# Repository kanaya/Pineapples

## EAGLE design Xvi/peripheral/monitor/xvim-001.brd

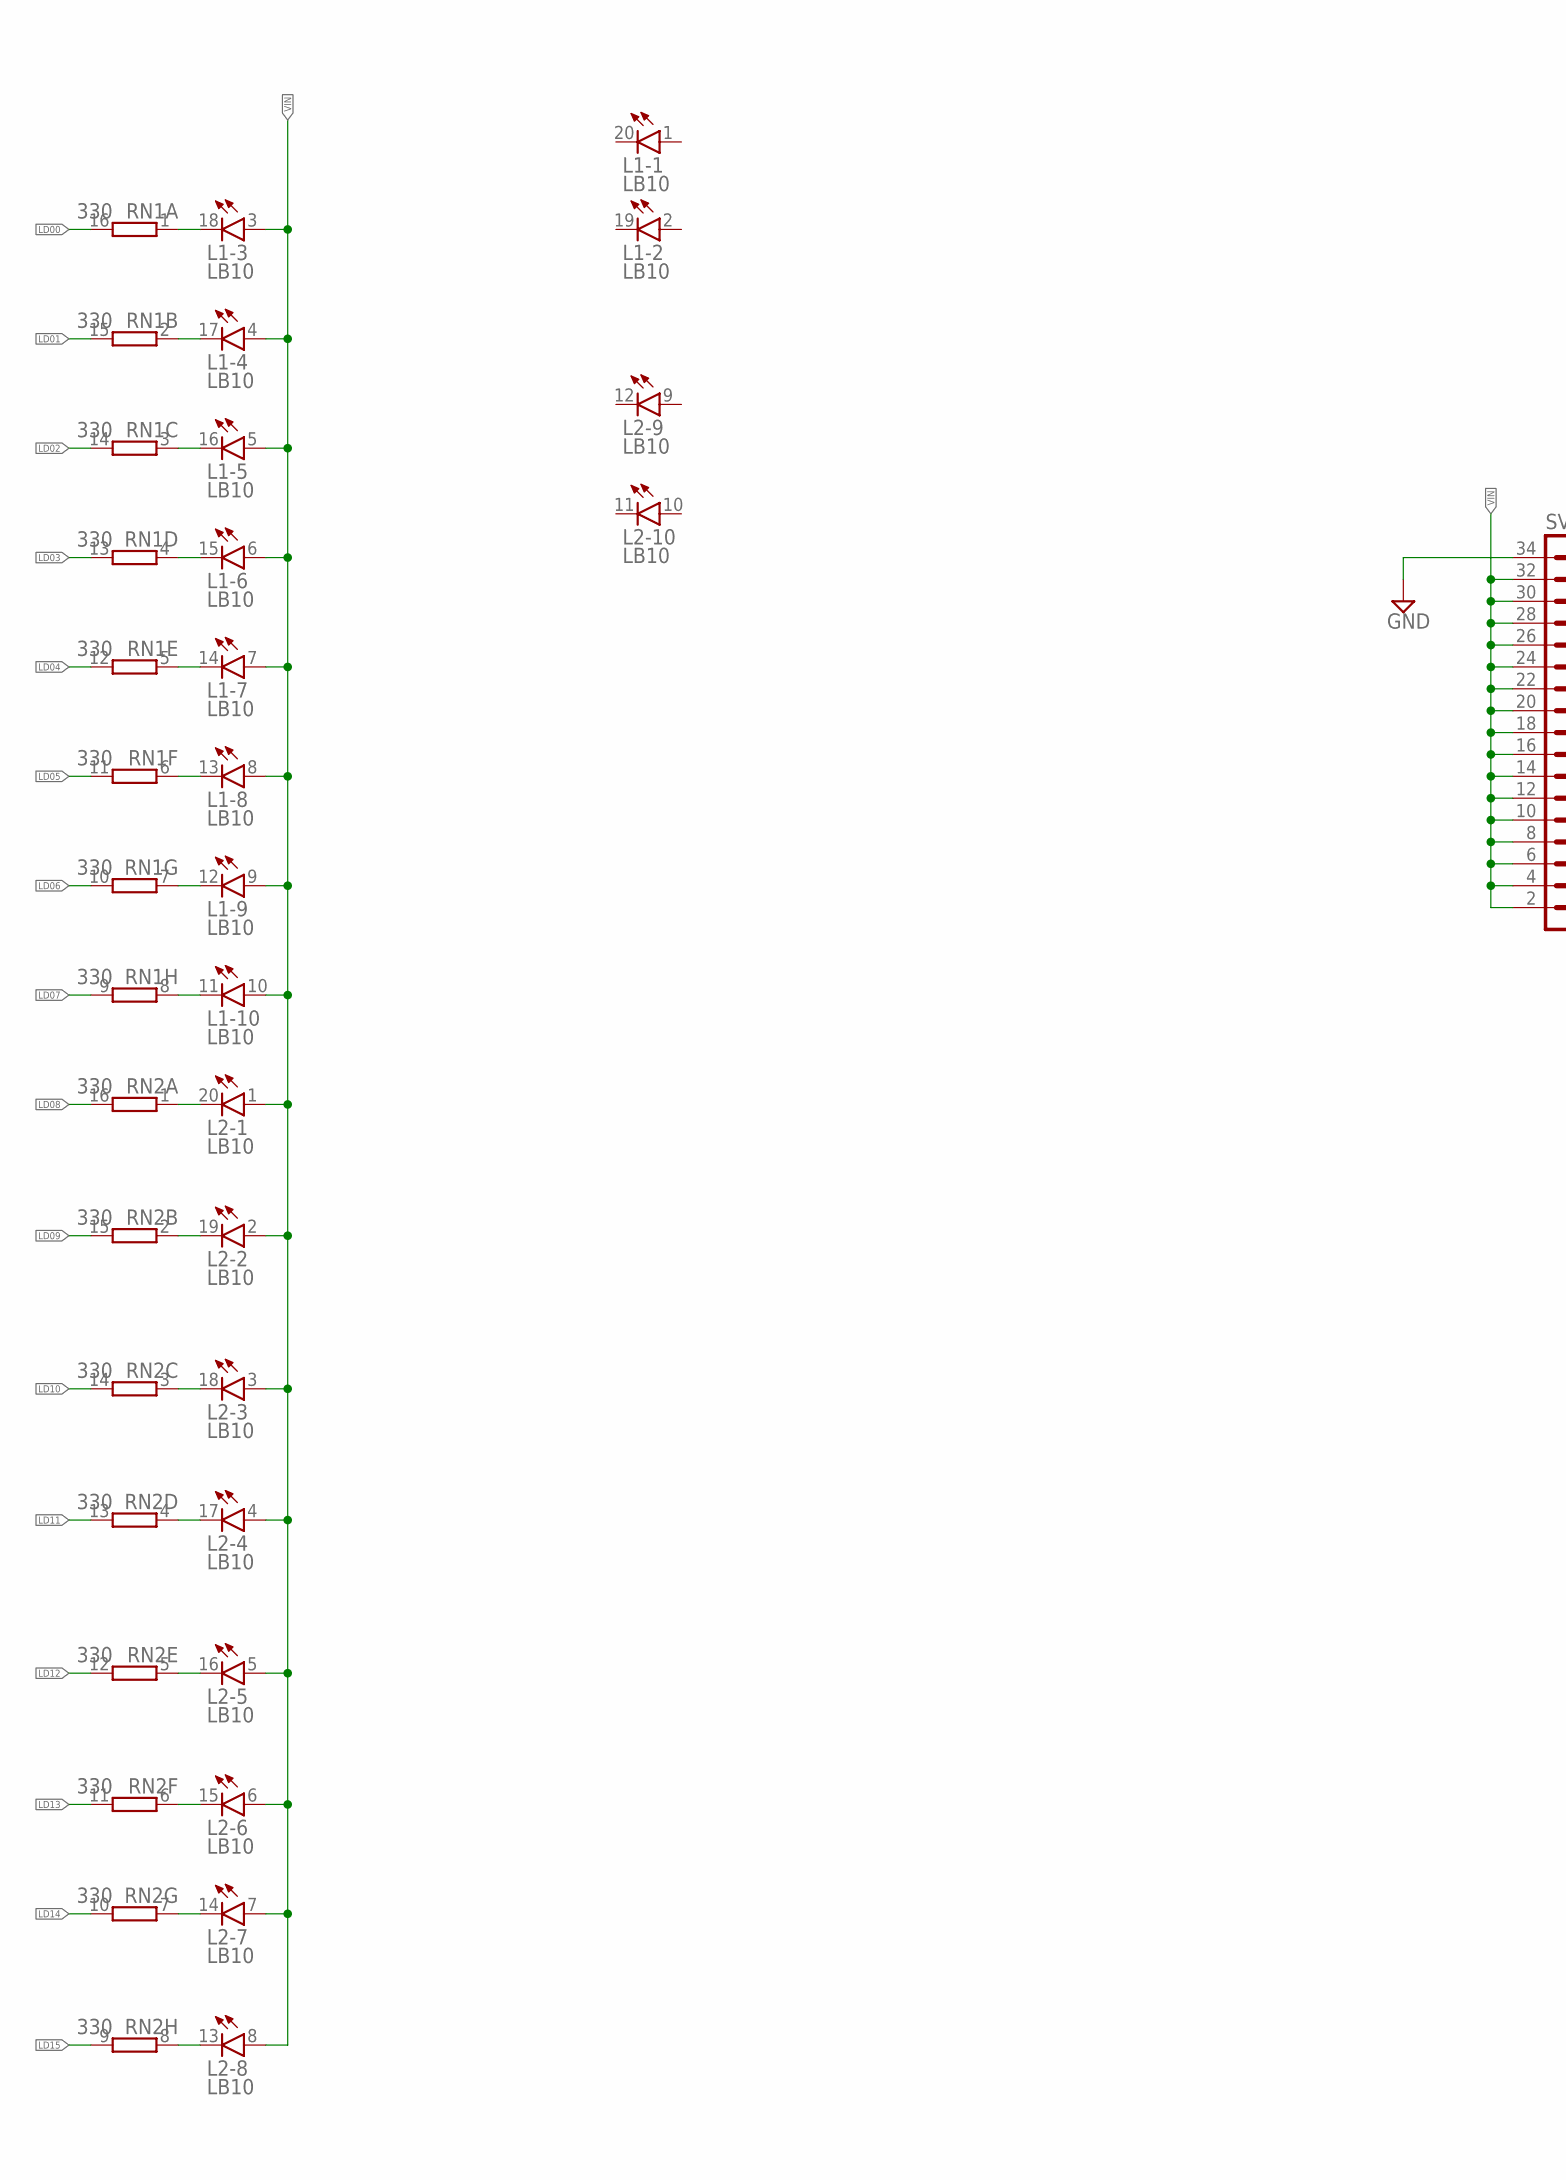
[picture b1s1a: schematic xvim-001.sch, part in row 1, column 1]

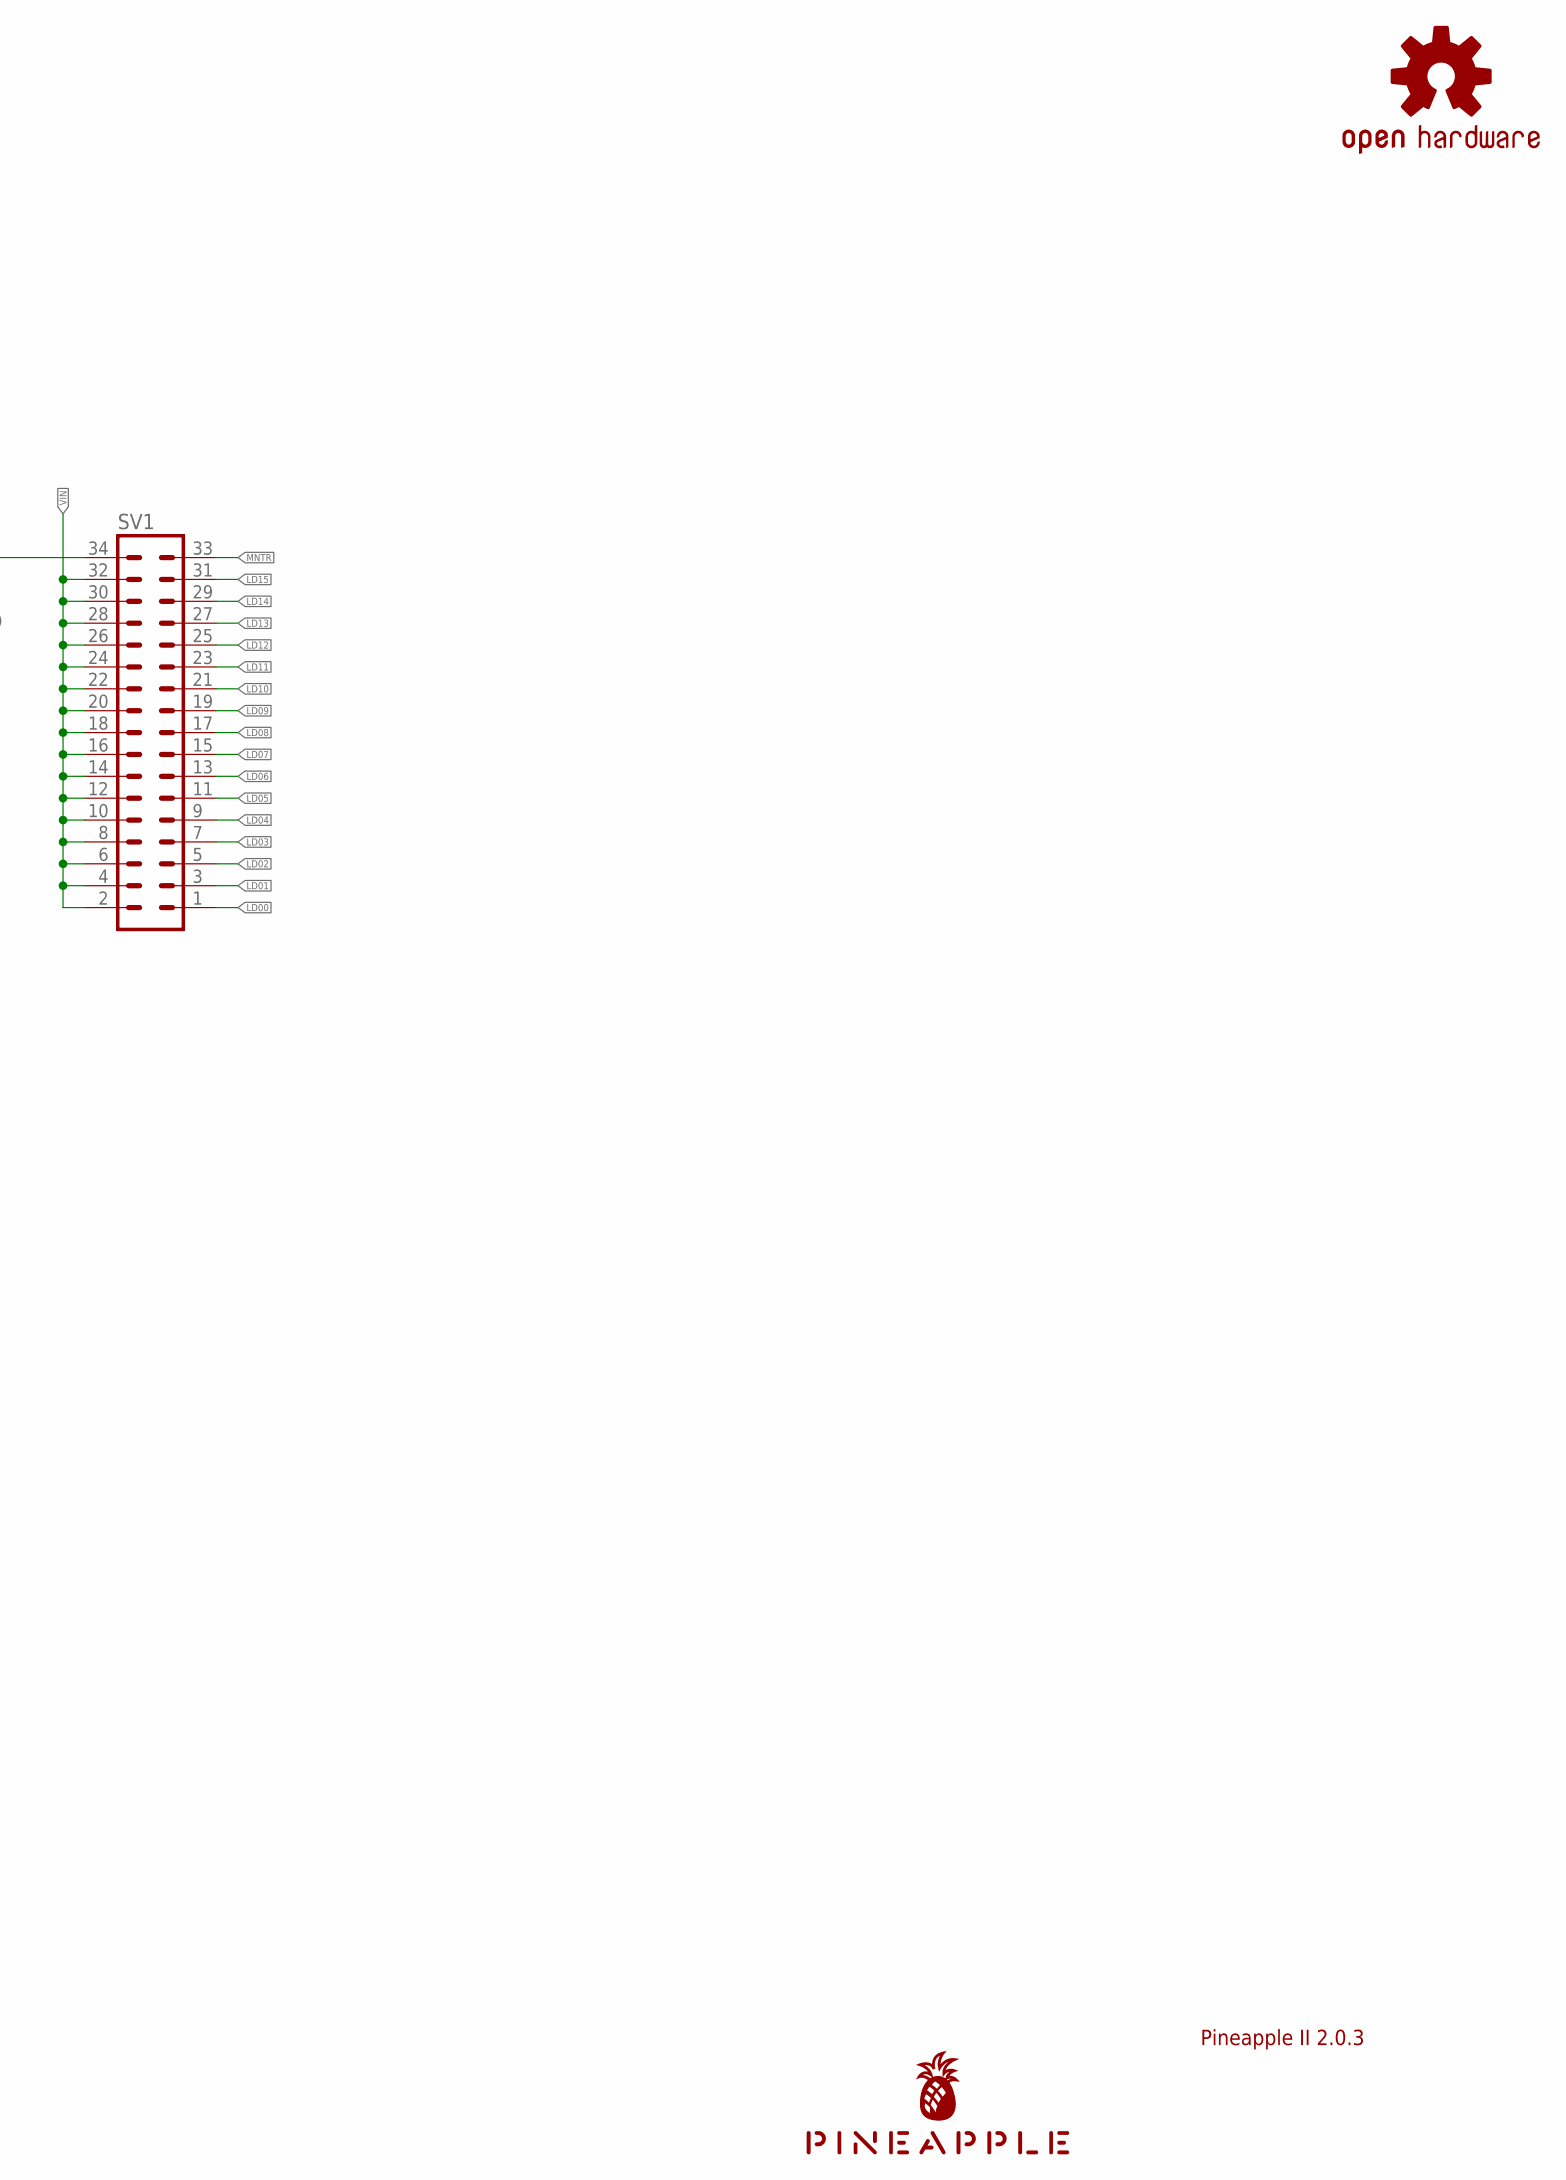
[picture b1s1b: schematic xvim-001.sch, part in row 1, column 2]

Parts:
L1, L2: LB10
LOGO1: OSHW-LOGOS-COPPER; OSHW-LOGO-S_COPPER
RN1, RN2: 330; DIL16
SV1: ML34L
U$1: PINEAPPLE450_SILK

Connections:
GND: SV1.34
LD00: RN1.16 (2), SV1.1
LD01: RN1.15 (2), SV1.3
LD02: RN1.14 (2), SV1.5
LD03: RN1.13 (2), SV1.7
LD04: RN1.12 (2), SV1.9
LD05: RN1.11 (2), SV1.11
LD06: RN1.10 (2), SV1.13
LD07: RN1.9 (2), SV1.15
LD08: RN2.16 (2), SV1.17
LD09: RN2.15 (2), SV1.19
LD10: RN2.14 (2), SV1.21
LD11: RN2.13 (2), SV1.23
LD12: RN2.12 (2), SV1.25
LD13: RN2.11 (2), SV1.27
LD14: RN2.10 (2), SV1.29
LD15: RN2.9 (2), SV1.31
MNTR: SV1.33
unnamed: L1.18 (C), RN1.1
unnamed: L1.17 (C), RN1.2 (1)
unnamed: L1.16 (C), RN1.3 (1)
unnamed: L1.15 (C), RN1.4 (1)
unnamed: L1.14 (C), RN1.5 (1)
unnamed: L1.13 (C), RN1.6 (1)
unnamed: L1.12 (C), RN1.7 (1)
unnamed: L1.11 (C), RN1.8 (1)
unnamed: L2.20 (C), RN2.1
unnamed: L2.19 (C), RN2.2 (1)
unnamed: L2.18 (C), RN2.3 (1)
unnamed: L2.17 (C), RN2.4 (1)
unnamed: L2.16 (C), RN2.5 (1)
unnamed: L2.15 (C), RN2.6 (1)
unnamed: L2.14 (C), RN2.7 (1)
unnamed: L2.13 (C), RN2.8 (1)
VIN: L1.3 (A), L1.4 (A), L1.5 (A), L1.6 (A), L1.7 (A), L1.8 (A), L1.9 (A), L1.10 (A), L2.1 (A), L2.2 (A), L2.3 (A), L2.4 (A), L2.5 (A), L2.6 (A), L2.7 (A), L2.8 (A), SV1.2, SV1.4, SV1.6, SV1.8, SV1.10, SV1.12, SV1.14, SV1.16, SV1.18, SV1.20, SV1.22, SV1.24, SV1.26, SV1.28, SV1.30, SV1.32

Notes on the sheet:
Pineapple II 2.0.3

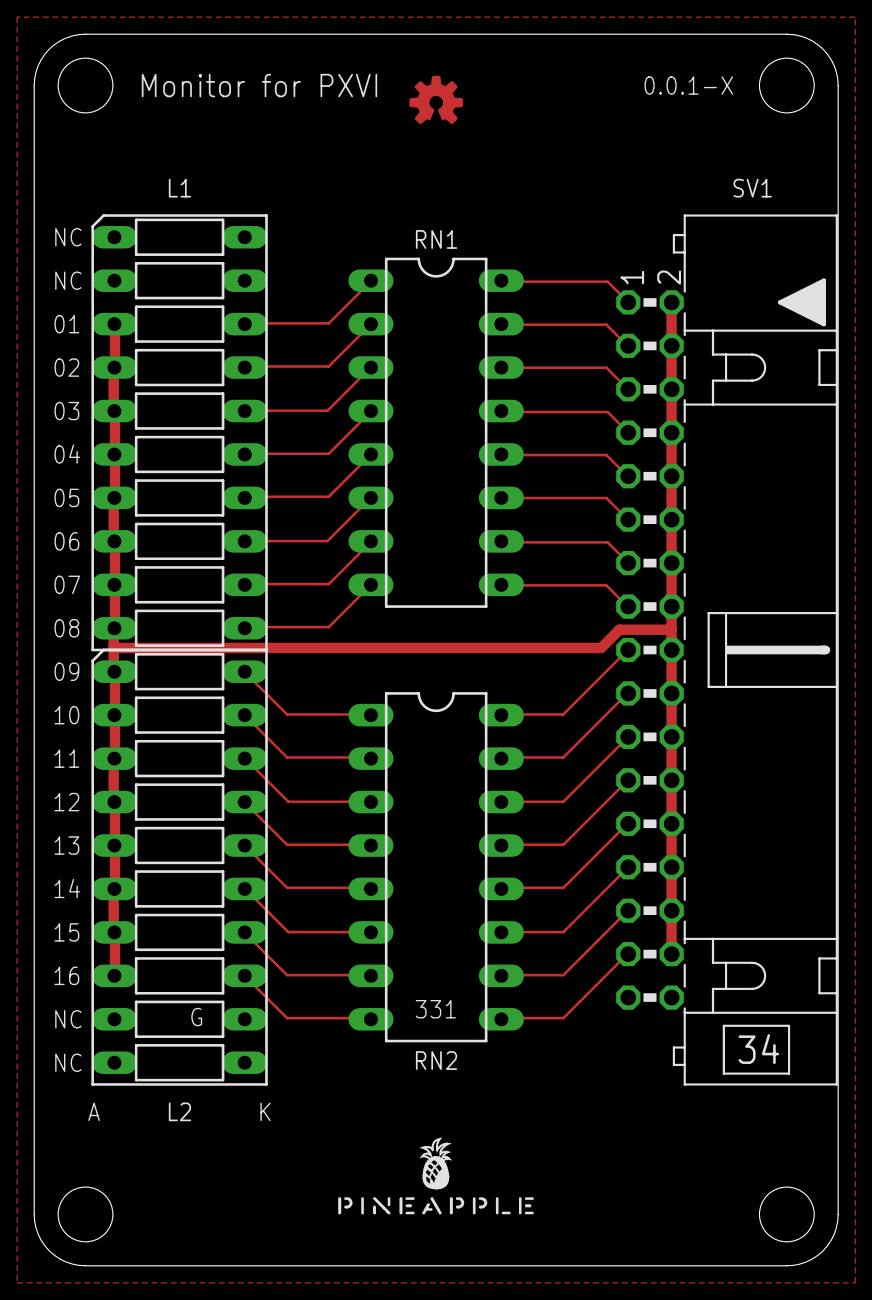
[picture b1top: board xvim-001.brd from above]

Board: 2 copper layers, 47.0 x 72.0 mm, 7 parts (0 on the bottom side), 33 nets.

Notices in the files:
parts and their libraries:
SparkFun-Aesthetics: Licensing: Creative Commons ShareAlike 4.0 International - https://creativecommons.org/licenses/by-sa/4.0
